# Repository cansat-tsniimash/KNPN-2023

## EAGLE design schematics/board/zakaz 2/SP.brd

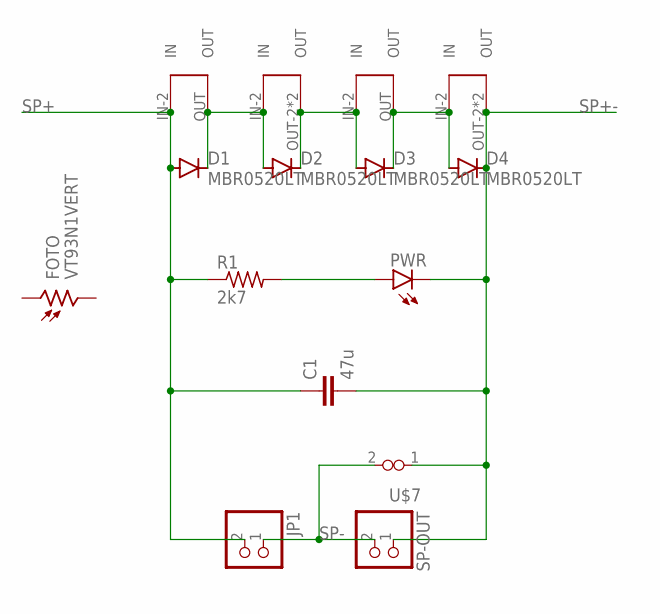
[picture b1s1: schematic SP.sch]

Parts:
C1: 47u; C1210
D1, D2, D3, D4: MBR0520LT; SOD123
FOTO: VT93N1VERT; VT93N1-VERT
JP1: PINHD-1X2; 1X02
PWR: LEDCHIP-LED0603; CHIP-LED0603
R1: 2k7; R0603
SP-OUT: PINHD-1X2; 1X02
U$1, U$3: SOLAR-2_1; SOLAR_1-2
U$2, U$4: SOLAR-2_0; SOLAR_0-2
U$7: VIAS-CONNECT

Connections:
unnamed: D1.C, D2.A, U$1.OUT, U$2.IN-2 (IN)
unnamed: D2.C, D3.A, U$2.OUT-2 (OUT), U$2.OUT-21 (OUT), U$3.IN-2 (IN)
unnamed: D3.C, D4.A, U$3.OUT, U$4.IN-2 (IN)
unnamed: PWR.A, R1.2
SP+: C1.1, D1.A, JP1.2, R1.1, U$1.IN-2 (IN)
SP+-: C1.2, D4.C, PWR.C, SP-OUT.1, U$4.OUT-2 (OUT), U$4.OUT-21 (OUT), U$7.1
SP-: JP1.1, SP-OUT.2, U$7.2

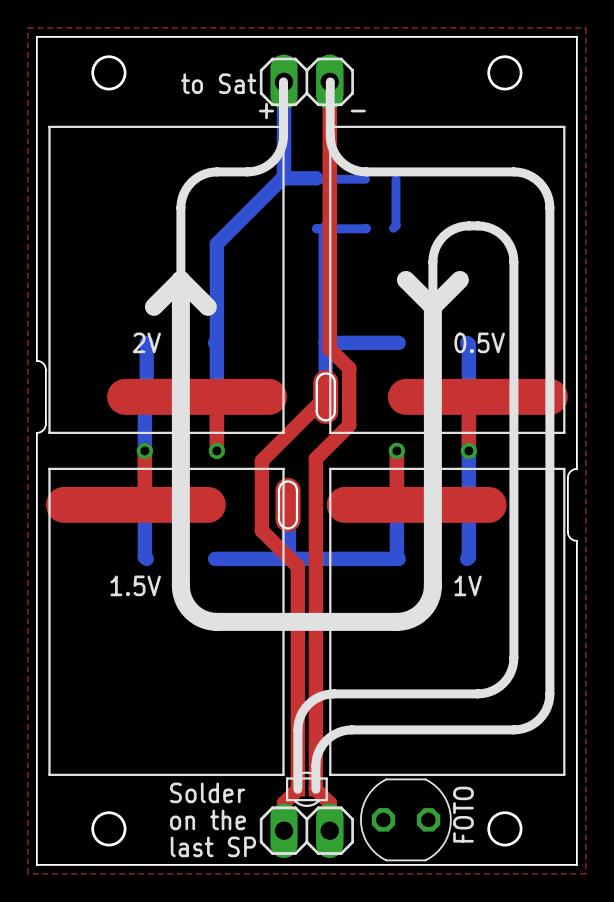
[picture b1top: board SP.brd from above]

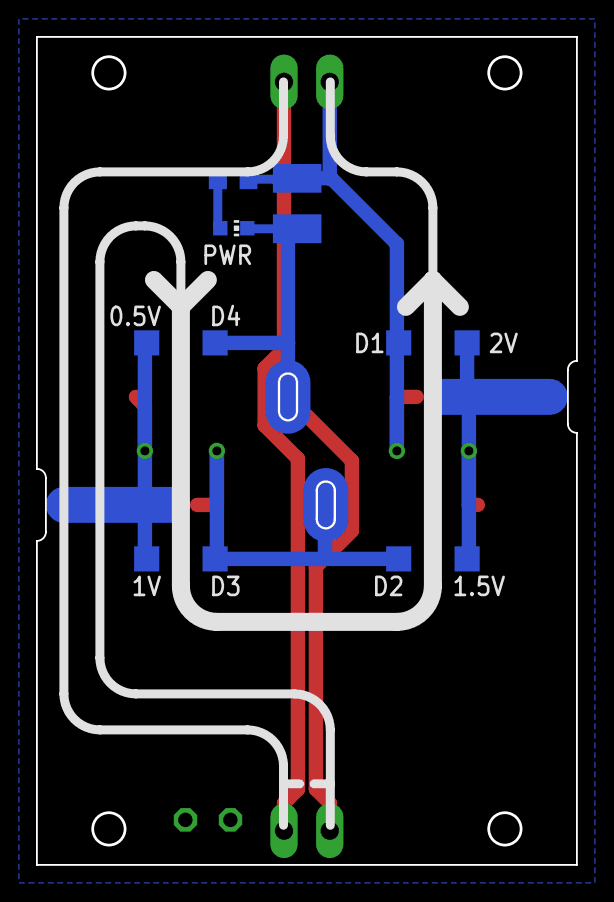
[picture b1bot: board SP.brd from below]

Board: 2 copper layers, 29.9 x 45.9 mm, 15 parts (7 on the bottom side), 7 nets.

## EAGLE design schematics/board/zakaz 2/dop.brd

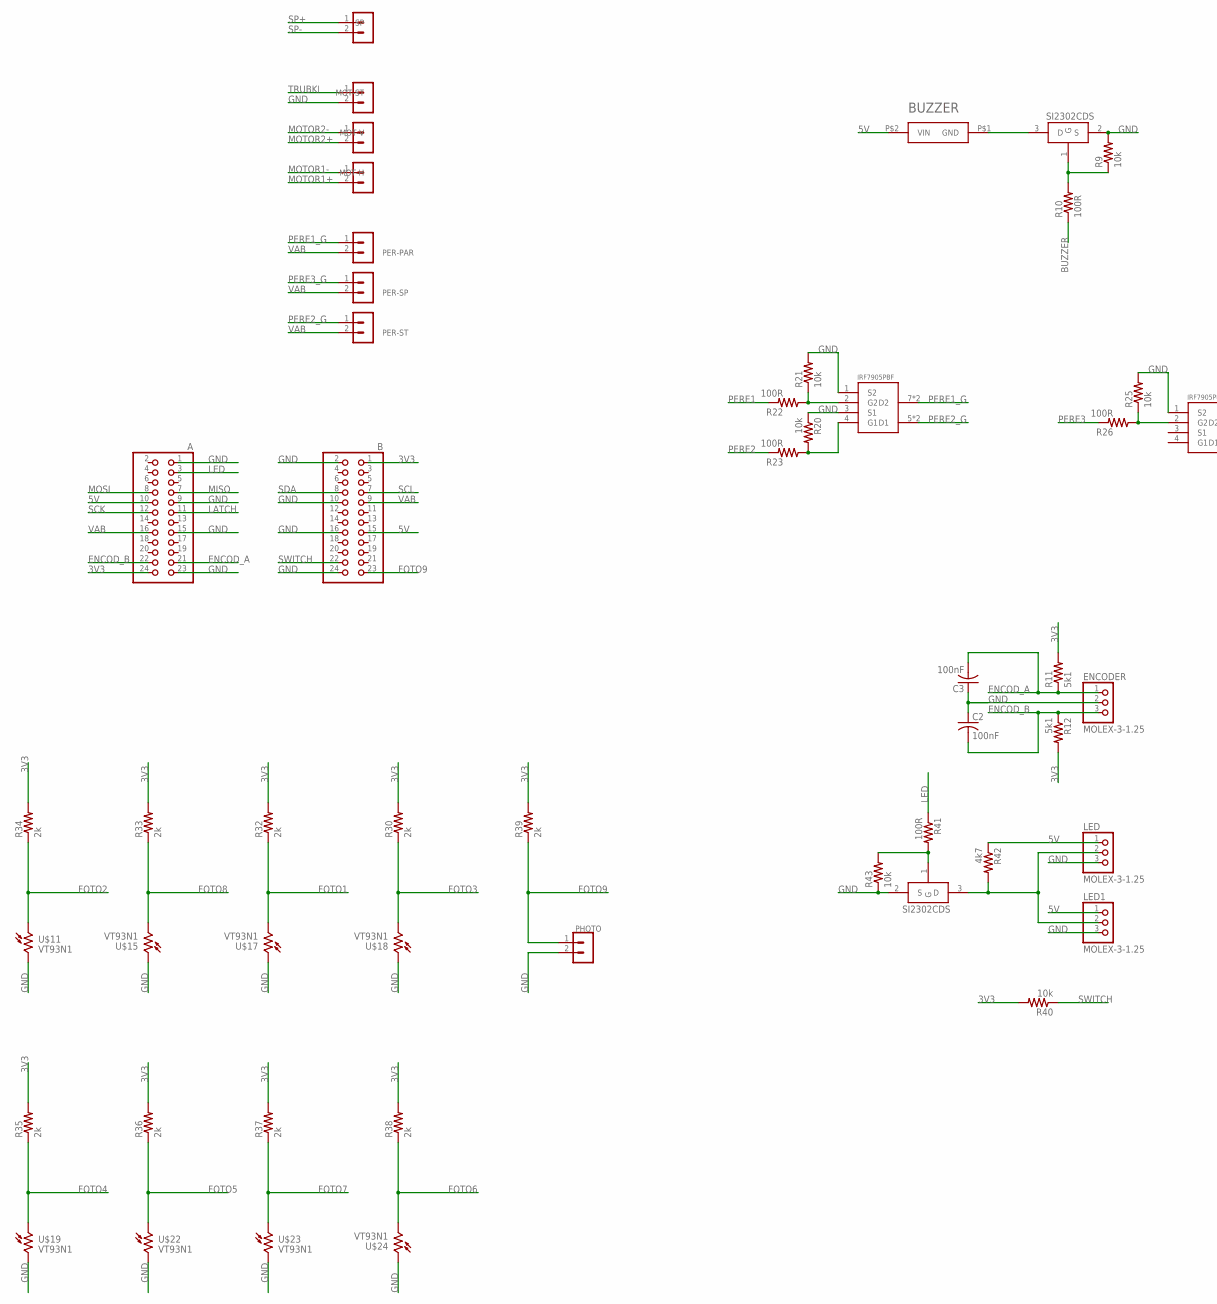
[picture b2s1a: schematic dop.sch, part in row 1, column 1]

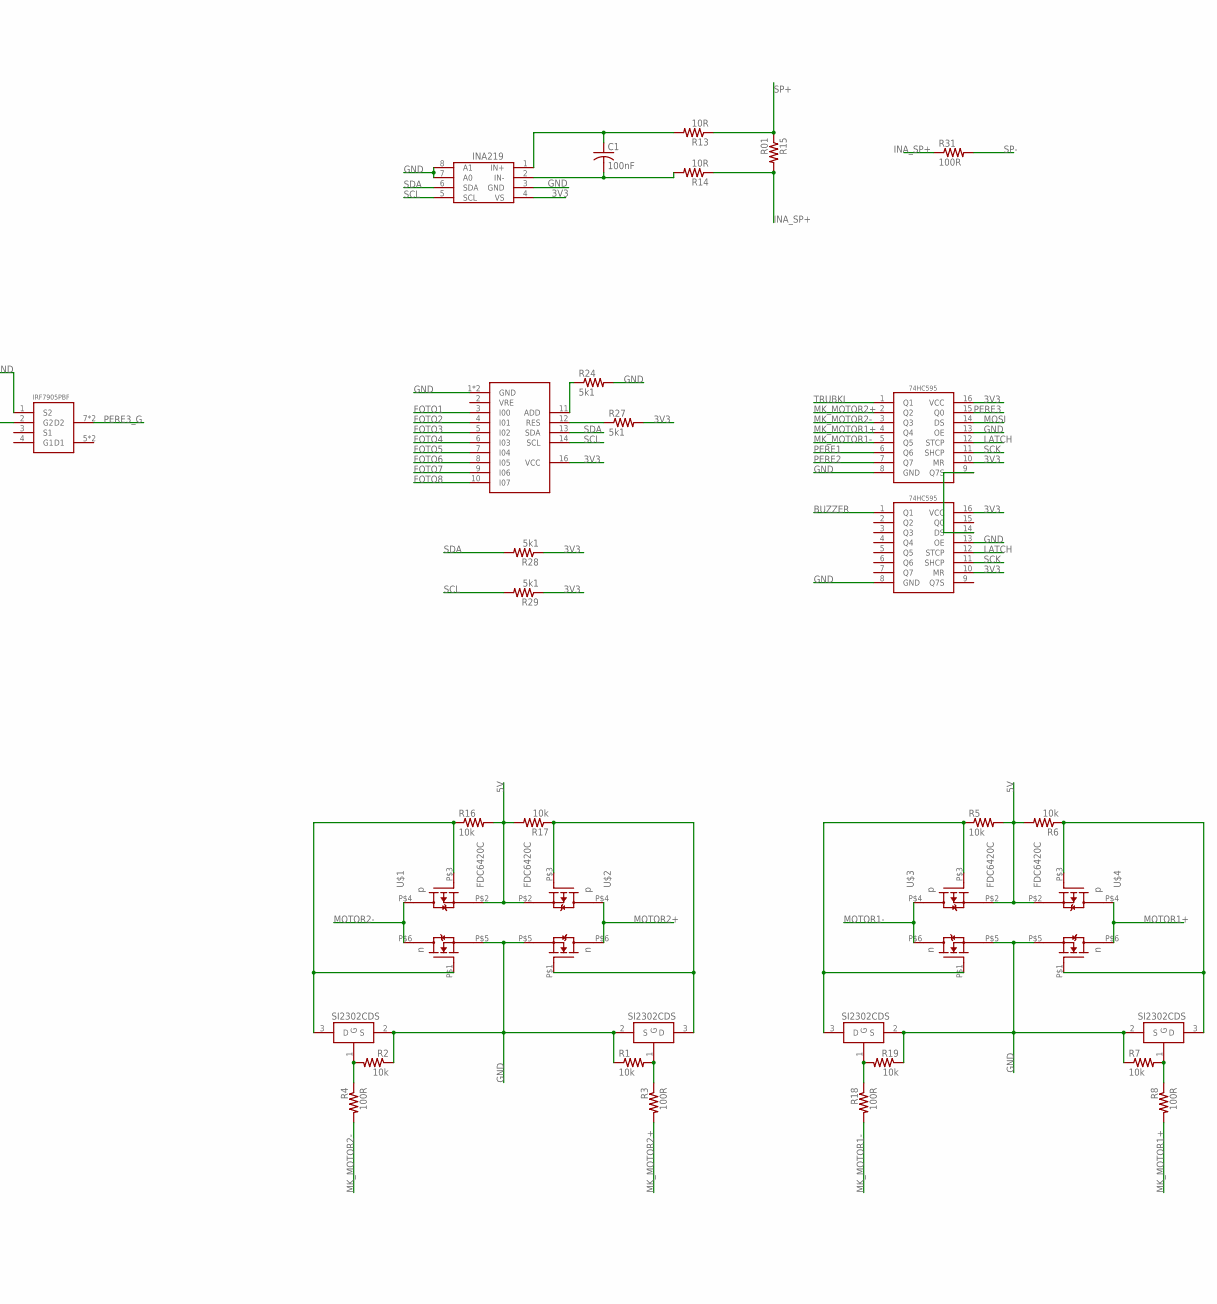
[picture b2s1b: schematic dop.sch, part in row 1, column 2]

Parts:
74HC595, 74HC595-: 74HC595; TSSOP16
A: PINHD-2X12; 2X12
AD5593: AD5593
B: PINHD-2X12; 2X12
BUZZER: BUZZERS8R6; BUZZER-S8R12
C1, C2, C3: 100nF; C0603
ENCODER: MOLEX-3-1.25; 53047-03
INA: INA219AID; SOT23-8
IRF7905, IRF7905-: IRF7905; SO8
LED, LED1: MOLEX-3-1.25; 53047-03
MOT-H: MOLEX-2-1.25; 53047-02
MOT-ST: MOLEX-2-1.25; 53047-02
MOT-V: MOLEX-2-1.25; 53047-02
PER-PAR: JST-2-2.5
PER-SP: JST-2-2.5
PER-ST: JST-2-2.5
PHOTO: MOLEX-2-1.25; 53047-02
R1, R2, R5, R6, R7, R9, R16, R17, R19, R20, R21, R25, R40, R43: 10k; R0603
R3, R4, R8, R10, R18, R22, R23, R26, R41: 100R; R0603
R11, R12, R24, R27, R28, R29: 5k1; R0603
R13, R14: 10R; R0603
R15: R01; R2512
R30, R32, R33, R34, R35, R36, R37, R38, R39: 2k; R0603
R31: 100R; 0207/15
R42: 4k7; R0603
SI2302, SI2302-, SI2302-1, SI2302-2, SI2302-3, SI2302-4: SI2302CDS; SOT23-3
SP: MOLEX-2-1.25; 53047-02
U$1, U$2, U$3, U$4: FDC6420C; TSOP-6
U$11, U$15, U$17, U$18, U$19, U$22, U$23, U$24: VT93N1

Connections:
3V3: 74HC595.10 (MR), 74HC595.16 (VCC), 74HC595-.10 (MR), 74HC595-.16 (VCC), A.24, AD5593.16 (VCC), B.1, INA.4 (VS), R11.2, R12.2, R27.2, R28.1, R29.1, R30.2, R32.2, R33.2, R34.2, R35.2, R36.2, R37.2, R38.2, R39.2, R40.2
5V: A.10, B.15, BUZZER.P$2 (VIN), LED.1, LED1.1, R5.2, R6.2, R16.2, R17.2, R42.1, U$1.P$2 (PS), U$2.P$2 (PS), U$3.P$2 (PS), U$4.P$2 (PS)
BUZZER: 74HC595-.1 (Q1), R10.1
ENCOD_A: A.21, C3.2, ENCODER.1, R11.1
ENCOD_B: A.22, C2.2, ENCODER.3, R12.1
FOTO1: AD5593.3 (I00), R32.1, U$17.P$2 (2)
FOTO2: AD5593.4 (I01), R34.1, U$11.P$1 (1)
FOTO3: AD5593.5 (I02), R30.1, U$18.P$2 (2)
FOTO4: AD5593.6 (I03), R35.1, U$19.P$1 (1)
FOTO5: AD5593.7 (I04), R36.1, U$22.P$1 (1)
FOTO6: AD5593.8 (I05), R38.1, U$24.P$2 (2)
FOTO7: AD5593.9 (I06), R37.1, U$23.P$1 (1)
FOTO8: AD5593.10 (I07), R33.1, U$15.P$2 (2)
FOTO9: B.23, PHOTO.1, R39.1
GND: 74HC595.8 (GND), 74HC595.13 (OE), 74HC595-.8 (GND), 74HC595-.13 (OE), A.1, A.9, A.15, A.23, AD5593.1 (GND), AD5593.15 (GND), B.2, B.10, B.16, B.24, C2.1, C3.1, ENCODER.2, INA.3 (GND), INA.7 (A0), INA.8 (A1), IRF7905.1 (S2), IRF7905.3 (S1), IRF7905-.1 (S2), LED.3, LED1.3, MOT-ST.2, PHOTO.2, R1.1, R2.1, R7.1, R9.2, R19.1, R20.1, R21.2, R24.2, R25.2, R43.1, SI2302.2 (S), SI2302-.2 (S), SI2302-1.2 (S), SI2302-2.2 (S), SI2302-3.2 (S), SI2302-4.2 (S), U$1.P$5 (NS), U$2.P$5 (NS), U$3.P$5 (NS), U$4.P$5 (NS), U$11.P$2 (2), U$15.P$1 (1), U$17.P$1 (1), U$18.P$1 (1), U$19.P$2 (2), U$22.P$2 (2), U$23.P$2 (2), U$24.P$1 (1)
INA_SP+: R14.1, R15.2, R31.1
LATCH: 74HC595.12 (STCP), 74HC595-.12 (STCP), A.11
LED: A.3, R41.1
MISO: A.7
MK_MOTOR1+: 74HC595.4 (Q4), R8.2
MK_MOTOR1-: 74HC595.5 (Q5), R18.2
MK_MOTOR2+: 74HC595.2 (Q2), R3.2
MK_MOTOR2-: 74HC595.3 (Q3), R4.2
MOSI: 74HC595.14 (DS), A.8
MOTOR1+: MOT-H.2, U$4.P$4 (PD), U$4.P$6 (ND)
MOTOR1-: MOT-H.1, U$3.P$4 (PD), U$3.P$6 (ND)
MOTOR2+: MOT-V.2, U$2.P$4 (PD), U$2.P$6 (ND)
MOTOR2-: MOT-V.1, U$1.P$4 (PD), U$1.P$6 (ND)
unnamed: R1.2, R3.1, SI2302-3.1 (G)
unnamed: R2.2, R4.1, SI2302-1.1 (G)
unnamed: R5.1, SI2302-2.3 (D), U$3.P$1 (NG), U$3.P$3 (PG)
unnamed: R7.2, R8.1, SI2302-4.1 (G)
unnamed: R18.1, R19.2, SI2302-2.1 (G)
unnamed: R6.1, SI2302-4.3 (D), U$4.P$1 (NG), U$4.P$3 (PG)
unnamed: IRF7905.4 (G1), R20.2, R23.1
unnamed: IRF7905.2 (G2), R21.1, R22.1
unnamed: BUZZER.P$1 (GND), SI2302-.3 (D)
unnamed: R9.1, R10.2, SI2302-.1 (G)
unnamed: C1.1, INA.1 (IN+), R13.2
unnamed: C1.2, INA.2 (IN-), R14.2
unnamed: R41.2, R43.2, SI2302.1 (G)
unnamed: AD5593.12 (RES), R27.1
unnamed: R17.1, SI2302-3.3 (D), U$2.P$1 (NG), U$2.P$3 (PG)
unnamed: AD5593.11 (ADD), R24.1
unnamed: IRF7905-.2 (G2), R25.1, R26.1
unnamed: 74HC595.9 (Q7S), 74HC595-.14 (DS)
unnamed: LED.2, LED1.2, R42.2, SI2302.3 (D)
unnamed: R16.1, SI2302-1.3 (D), U$1.P$1 (NG), U$1.P$3 (PG)
PERE1: 74HC595.6 (Q6), R22.2
PERE1_G: IRF7905.7 (D2), IRF7905.8 (D2), PER-PAR.1
PERE2: 74HC595.7 (Q7), R23.2
PERE2_G: IRF7905.5 (D1), IRF7905.6 (D1), PER-ST.1
PERE3: 74HC595.15 (Q0), R26.2
PERE3_G: IRF7905-.7 (D2), IRF7905-.8 (D2), PER-SP.1
SCK: 74HC595.11 (SHCP), 74HC595-.11 (SHCP), A.12
SCL: AD5593.14 (SCL), B.7, INA.5 (SCL), R29.2
SDA: AD5593.13 (SDA), B.8, INA.6 (SDA), R28.2
SP+: R13.1, R15.1, SP.1
SP-: R31.2, SP.2
SWITCH: B.22, R40.1
TRUBKI: 74HC595.1 (Q1), MOT-ST.1
VAB: A.16, B.9, PER-PAR.2, PER-SP.2, PER-ST.2

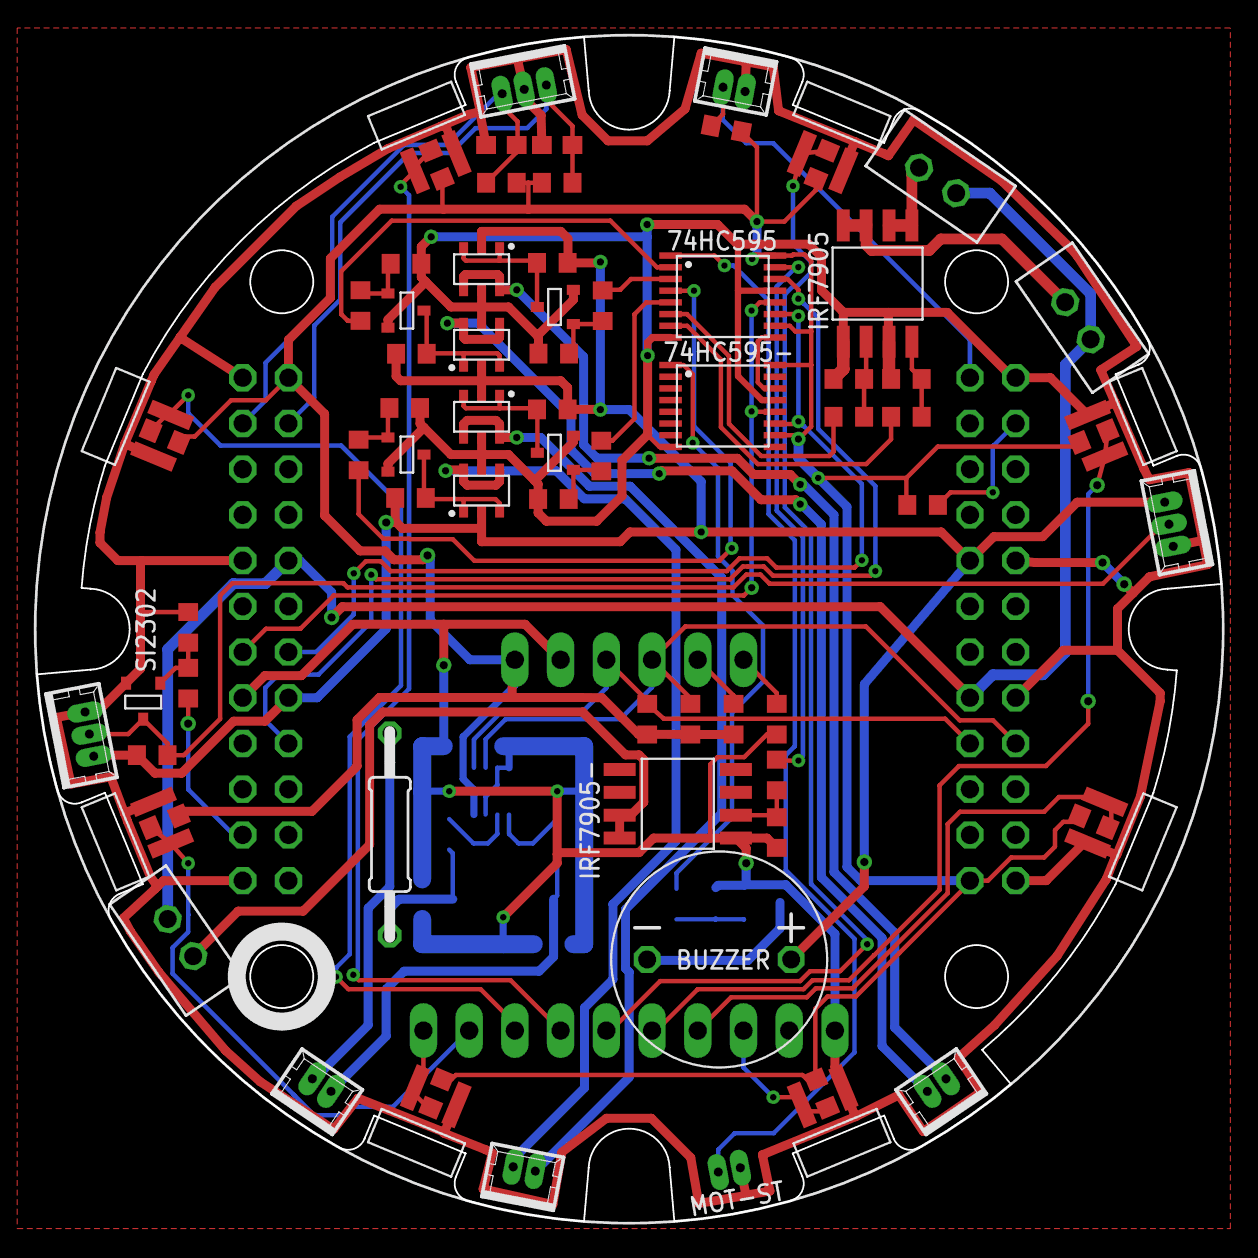
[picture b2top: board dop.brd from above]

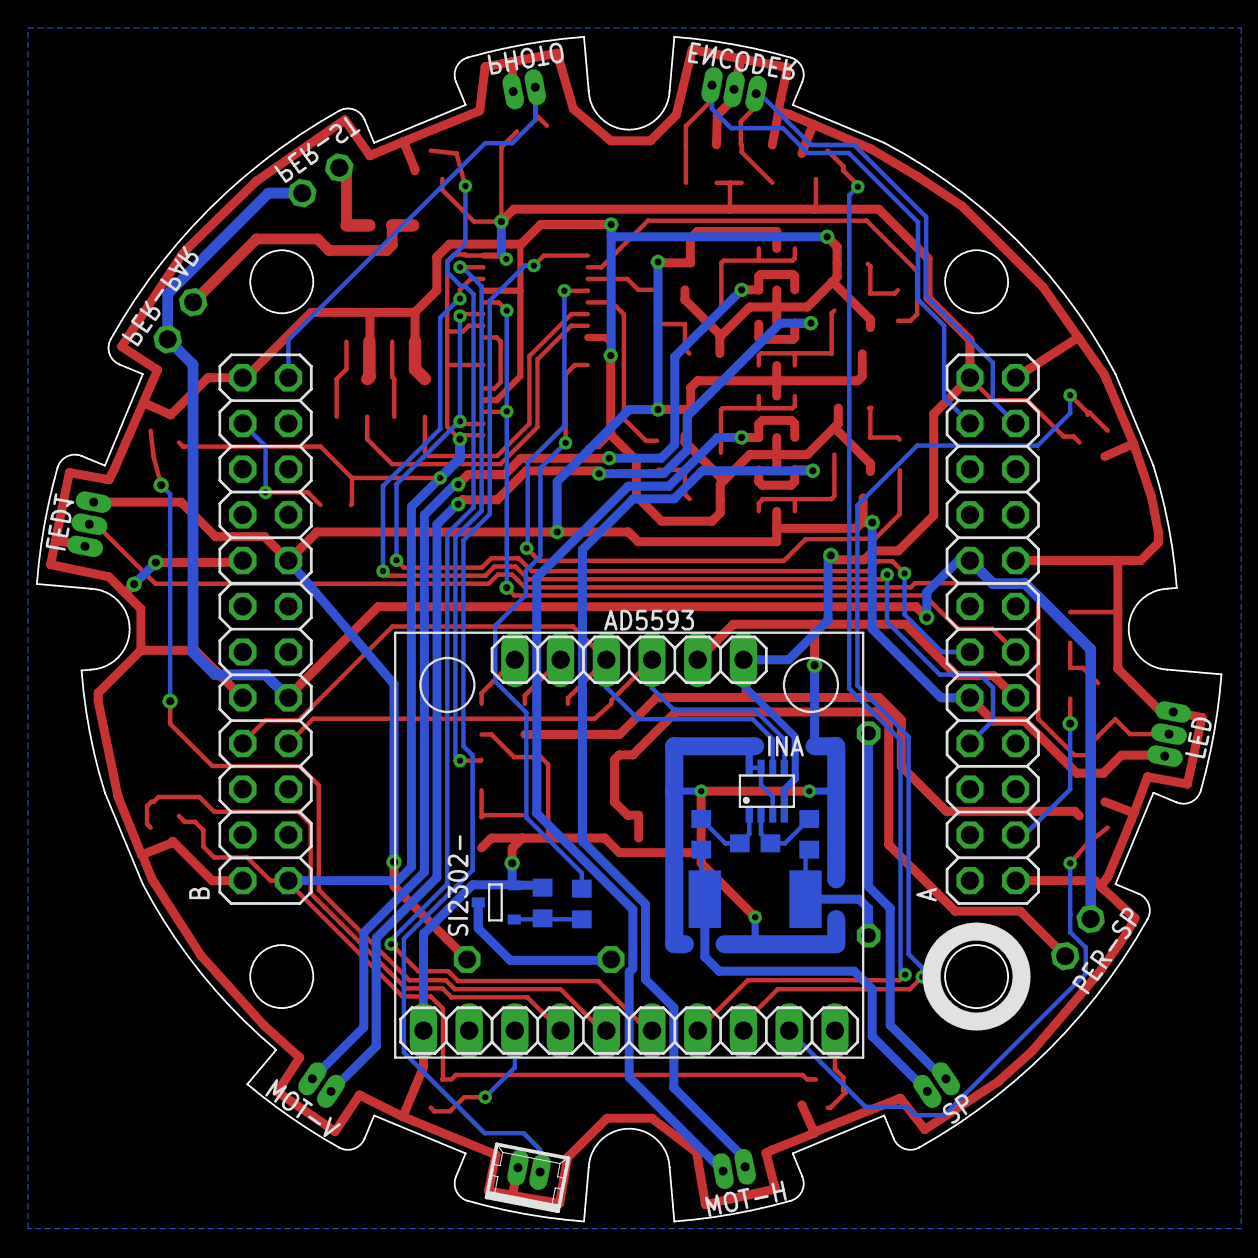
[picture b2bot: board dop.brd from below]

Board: 2 copper layers, 65.8 x 65.8 mm, 84 parts (12 on the bottom side), 61 nets.

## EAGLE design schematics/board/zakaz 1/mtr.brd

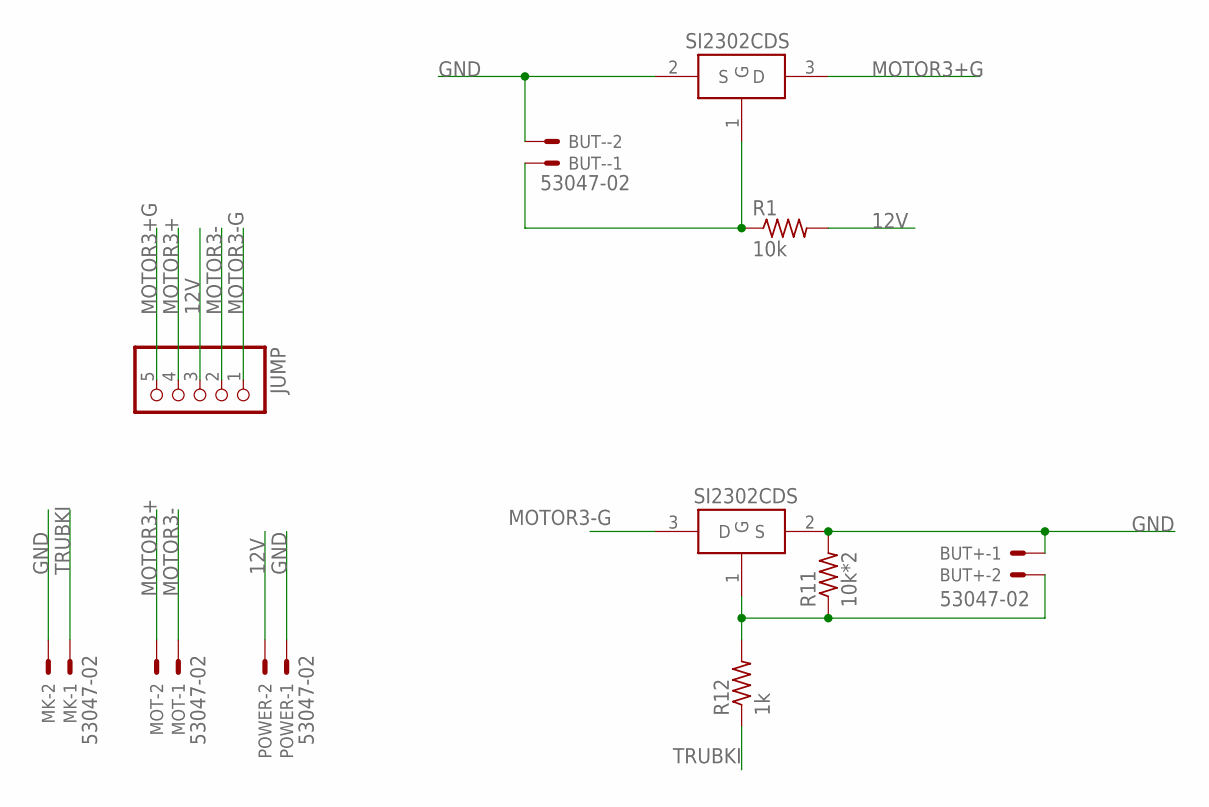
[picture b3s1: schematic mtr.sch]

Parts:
BUT+: 53047-02
BUT-: 53047-02
JUMP: PINHD-1X5; 1X05
MK: 53047-02
MOT: 53047-02
POWER: 53047-02
R1: 10k; R0603
R11: 10k*2; R0603
R12: 1k; R0603
U$1, U$21: SI2302CDS; SOT23-3

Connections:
12V: JUMP.3, POWER.2, R1.2
GND: BUT+.1, BUT-.2, MK.2, POWER.1, R11.2, U$1.2 (S), U$21.2 (S)
MOTOR3+: JUMP.4, MOT.2
MOTOR3+G: JUMP.5, U$21.3 (D)
MOTOR3-: JUMP.2, MOT.1
MOTOR3-G: JUMP.1, U$1.3 (D)
unnamed: BUT-.1, R1.1, U$21.1 (G)
unnamed: BUT+.2, R11.1, R12.2, U$1.1 (G)
TRUBKI: MK.1, R12.1

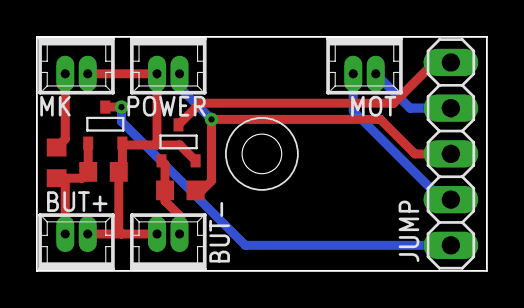
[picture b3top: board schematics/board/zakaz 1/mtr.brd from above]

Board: 2 copper layers, 25.0 x 13.0 mm, 11 parts (0 on the bottom side), 9 nets.

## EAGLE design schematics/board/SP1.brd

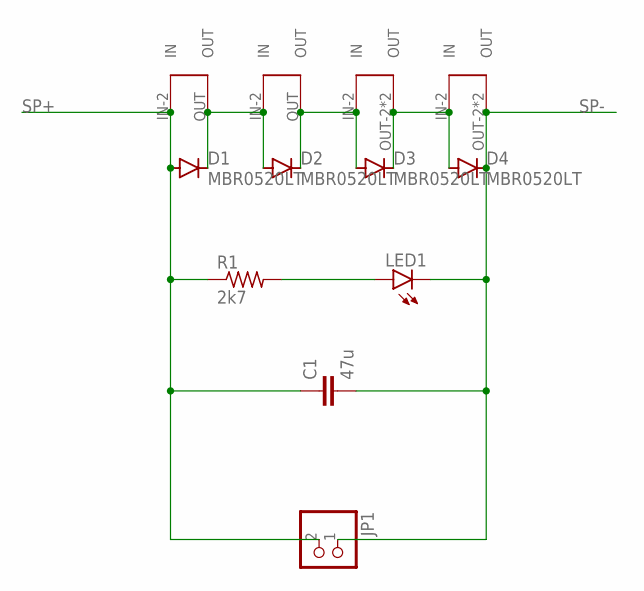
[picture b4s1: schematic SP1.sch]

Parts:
C1: 47u; C1210
D1, D2, D3, D4: MBR0520LT; SOD123
JP1: PINHD-1X2; 1X02
LED1: LEDCHIP-LED0603; CHIP-LED0603
R1: 2k7; R0603
U$1, U$2: SOLAR-2_1; SOLAR_1-2
U$3, U$4: SOLAR-2_0; SOLAR_0-2

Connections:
unnamed: D1.C, D2.A, U$1.OUT, U$2.IN-2 (IN)
unnamed: D2.C, D3.A, U$2.OUT, U$3.IN-2 (IN)
unnamed: D3.C, D4.A, U$3.OUT-2 (OUT), U$3.OUT-21 (OUT), U$4.IN-2 (IN)
unnamed: LED1.A, R1.2
SP+: C1.1, D1.A, JP1.2, R1.1, U$1.IN-2 (IN)
SP-: C1.2, D4.C, JP1.1, LED1.C, U$4.OUT-2 (OUT), U$4.OUT-21 (OUT)

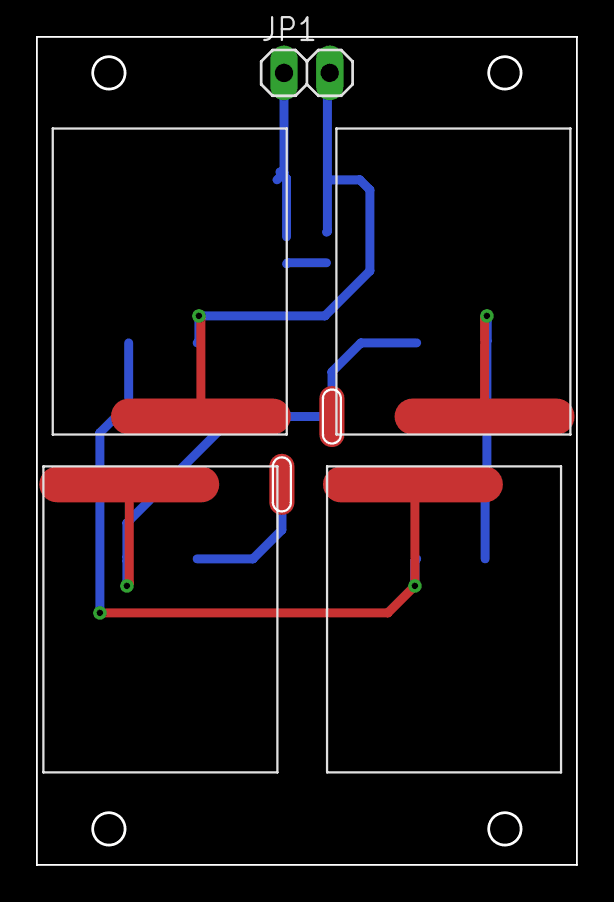
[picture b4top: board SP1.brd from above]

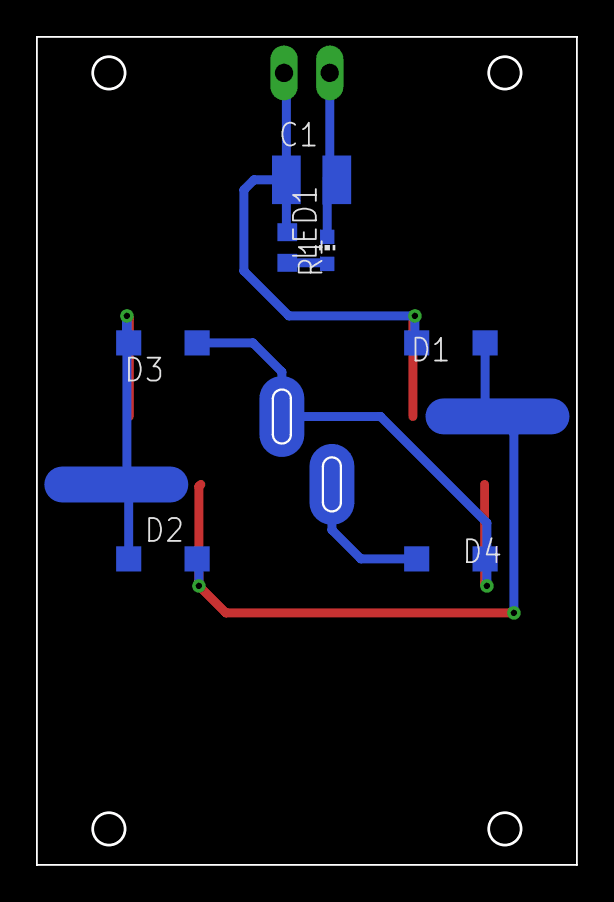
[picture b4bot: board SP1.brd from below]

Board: 2 copper layers, 29.9 x 45.9 mm, 12 parts (7 on the bottom side), 6 nets.

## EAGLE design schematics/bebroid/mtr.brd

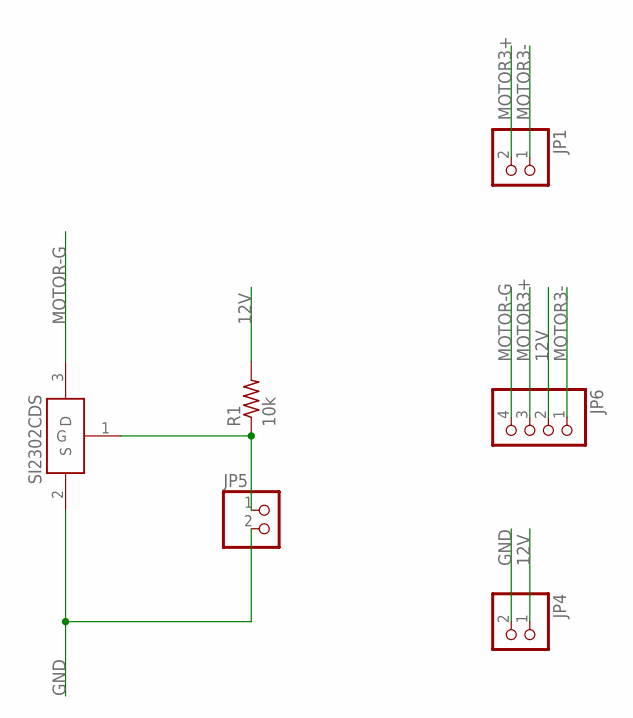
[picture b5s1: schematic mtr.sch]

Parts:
JP1, JP4, JP5: PINHD-1X2; 1X02
JP6: PINHD-1X4; 1X04
R1: 10k; R0603
U$21: SI2302CDS

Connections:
12V: JP4.1, JP6.2, R1.2
GND: JP4.2, JP5.2, U$21.2 (S)
MOTOR3+: JP1.2, JP6.3
MOTOR3-: JP1.1, JP6.1
MOTOR-G: JP6.4, U$21.3 (D)
unnamed: JP5.1, R1.1, U$21.1 (G)

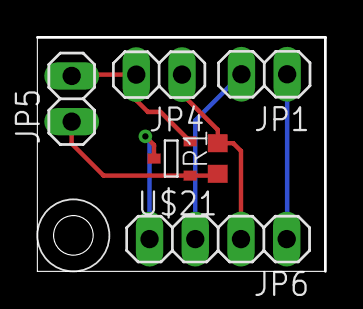
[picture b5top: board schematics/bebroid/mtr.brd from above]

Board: 2 copper layers, 16.0 x 13.0 mm, 6 parts (0 on the bottom side), 6 nets.

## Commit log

2023-02-04 Сабмодули
2023-02-11 код на LIS, LSM, BMP, начали радио
2023-02-11 начали делать доп. плату
2023-02-16 Удалили плату
2023-02-16 продолжаем делать доп плату
2023-02-16 Добавили фоторезистор в библиотеку
2023-02-17 Убрали дебаг + прописали путь
2023-02-17 добавил фоторезисторы на плату
2023-02-18 добавил фоторезистор и ds , начал заполнять пакеты радио
2023-02-18 начали писать код на наземку
2023-02-18 я шпион спорадика, почти забацал плату доп
2023-02-19 Закинула все модели creo в папку construction
2023-02-19 Добавили стопор двигателя для трубок
2023-02-23 Создали stl нижней части
2023-02-23 Сделали новую плату для кнопок на нижнем двигателе
2023-02-24 заполнил 3 пакета и добавил crc
2023-03-03 Начали делать платы СП
2023-03-03 Добавлены пружины для отделения парашюта
2023-03-03 Файлы stl перемещены в папку stl
2023-03-04 развёл плату солнечных панелей(на деньги)
2023-03-04 всё плохо ):
2023-03-11 добавил ину(всё плохо)
2023-03-16 Ина работает и откалибрована (коэффициент не потребовался)
2023-03-18 Радио шлет, принимаем мало
2023-03-18 ина больше не работает :(
2023-03-18 ина пашет как не в себя
2023-03-22 Доделаны платы dop и mtr
2023-03-22 Добавлена плата мотора в сборку
2023-03-25 Вроде бы то закомитил. Проверяйте
2023-03-25 Добавлен счетчик энкодера
2023-03-25 Подготовлены платы SP и mtr
2023-03-25 энкодер
2023-03-26 Подготовлена плата dop
2023-04-06 SD работает, но в csv иногда пишет лишнее
2023-04-08 Обновления в моделях
2023-04-08 радио работает но медленно и onewire не работает :(
2023-04-13 Демо-проект для съема показаний с энкодера
2023-05-03 чёта
2023-05-03 начал писать gps
2023-05-13 надеюсь будет работать
2023-05-20 ацп работает (Василий спасибо)
2023-05-25 попытка не пытка
2023-05-26 Написали навдение по двум осям
2023-05-27 Обновления в модели
2023-05-27 Обновления в платах
2023-05-27 Добавлен файл гитигнор
2023-06-02 esrrdcfugvkldf,g
2023-06-03 АЦП в аппарате не работает
2023-06-04 Новые версии плат
2023-06-05 STL для печати облегченной модели
2023-06-05 Облегчение модели
2023-06-10 Ина на плате работет. Коэффициенты: для тока (0,67034), для напряжения (1,0399).
2023-06-23 ну оно работало, а теперь нет :(
2023-06-25 Радио шлет первые пакеты на мощности -6dBm. На большей видимо не хватает питания
2023-06-26 Высота норм, фоторезистор норм. Не переходит в 4 состояние.
2023-06-27 Исправили циклы в 3 и 4 состояниях
2023-06-29 Состояния работают
2023-06-30 Пока все работает
2023-07-01 иуууууууууууууууууууууууууууууууууууууууууууууууууу готово все с кайфом :D
2023-07-02 Актуальные модели
